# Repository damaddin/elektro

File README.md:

# elektro
Some electronic circuits I made.

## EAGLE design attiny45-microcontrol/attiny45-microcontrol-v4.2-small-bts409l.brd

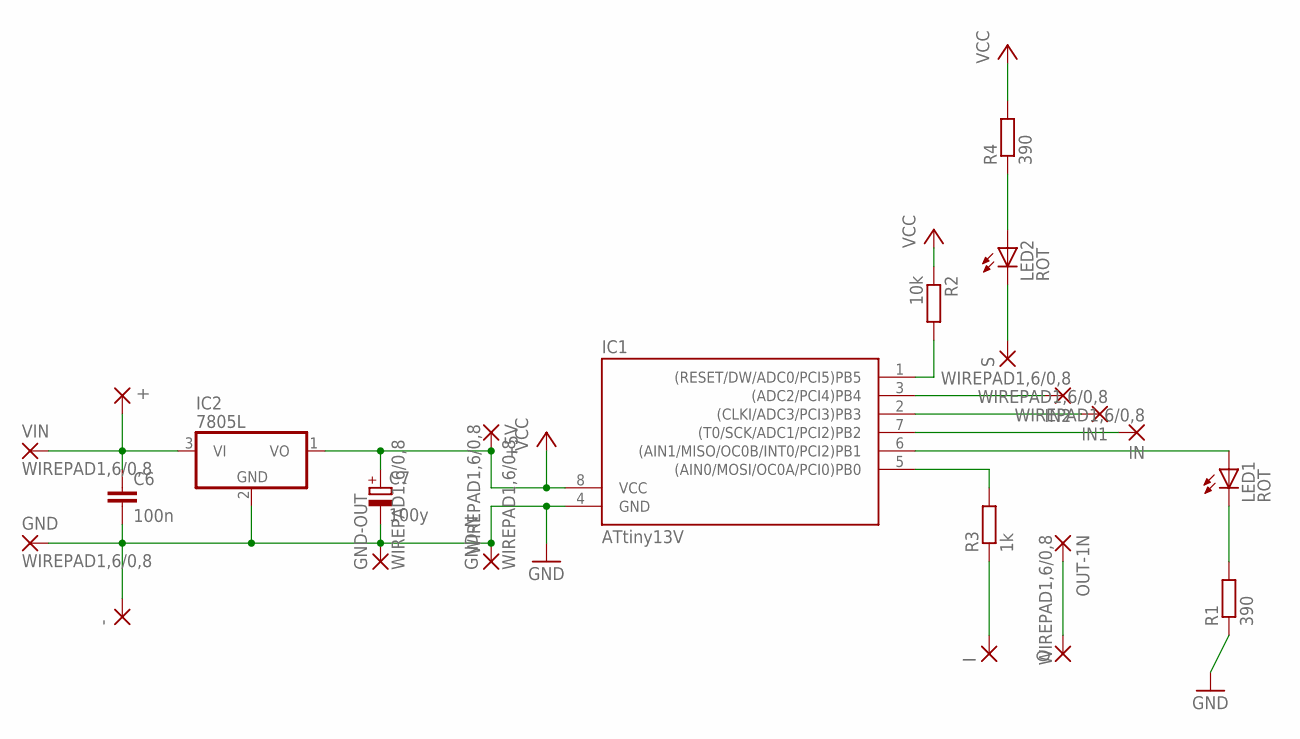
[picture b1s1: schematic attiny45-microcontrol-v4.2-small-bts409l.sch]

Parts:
+: SMD2; SMD1,27-2,54
+5V: WIREPAD1,6/0,8; 1,6/0,8
-: SMD2; SMD1,27-2,54
C6: 100n; C050-035X075
C7: 100y; E2,5-5
GND: WIREPAD1,6/0,8; 1,6/0,8
GND-N: WIREPAD1,6/0,8; 1,6/0,8
GND-OUT: WIREPAD1,6/0,8; 1,6/0,8
I: SMD2; SMD1,27-2,54
IC1: ATtiny13V; DIL08
IC2: 7805L; TO92
IN, IN1, IN2: WIREPAD1,6/0,8; 1,6/0,8
LED1, LED2: ROT; LED3MM
O: SMD2; SMD1,27-2,54
OUT-1N: WIREPAD1,6/0,8; 1,6/0,8
R1, R4: 390; 0204/5
R2: 10k; R1206
R3: 1k; 0207/7
S: SMD2; SMD1,27-2,54
VIN: WIREPAD1,6/0,8; 1,6/0,8

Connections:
GND: -.1, C6.2, C7.-, GND.1, GND-N.1, GND-OUT.1, IC1.4 (GND), IC2.2 (GND), R1.1
unnamed: O.1, OUT-1N.1
unnamed: IC1.2 ((CLKI/ADC3/PCI3)PB3), IN1.1
unnamed: IC1.1 ((RESET/DW/ADC0/PCI5)PB5), R2.2
unnamed: IC1.7 ((T0/SCK/ADC1/PCI2)PB2), IN.1
unnamed: IC1.6 ((AIN1/MISO/OC0B/INT0/PCI2)PB1), LED1.A
unnamed: LED1.K (C), R1.2
unnamed: IC1.3 ((ADC2/PCI4)PB4), IN2.1
unnamed: LED2.A, R4.1
unnamed: IC1.5 ((AIN0/MOSI/OC0A/PCI0)PB0), R3.2
unnamed: I.1, R3.1
unnamed: LED2.K (C), S.1
unnamed: +.1, C6.1, IC2.3 (VI), VIN.1
VCC: +5V.1, C7.+, IC1.8 (VCC), IC2.1 (VO), R2.1, R4.2

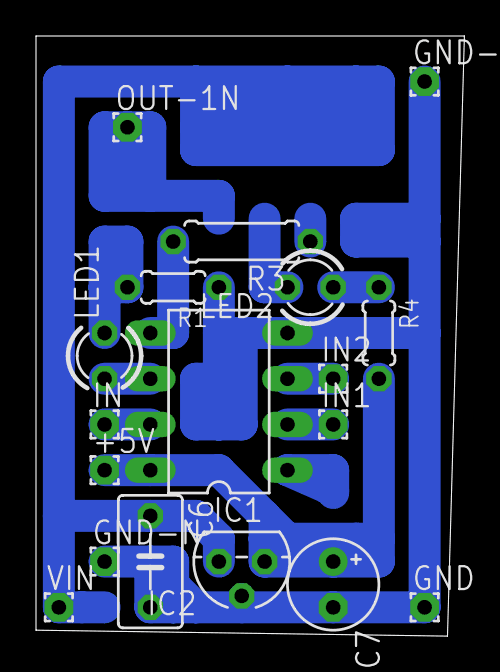
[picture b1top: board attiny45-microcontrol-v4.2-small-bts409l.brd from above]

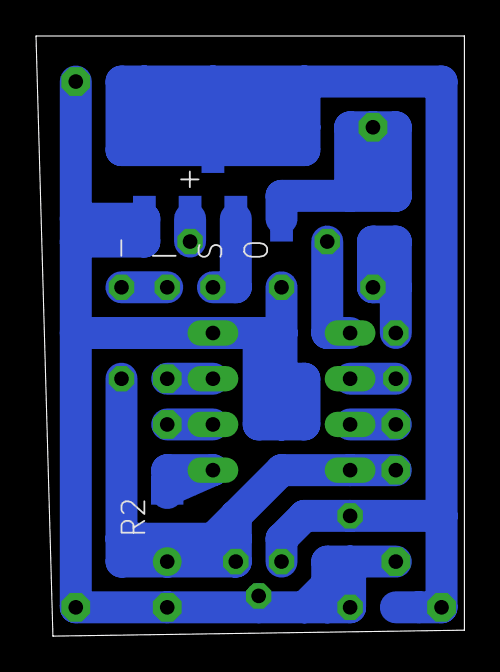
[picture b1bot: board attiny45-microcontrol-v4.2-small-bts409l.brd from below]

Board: 2 copper layers, 23.8 x 33.3 mm, 24 parts (6 on the bottom side), 14 nets.

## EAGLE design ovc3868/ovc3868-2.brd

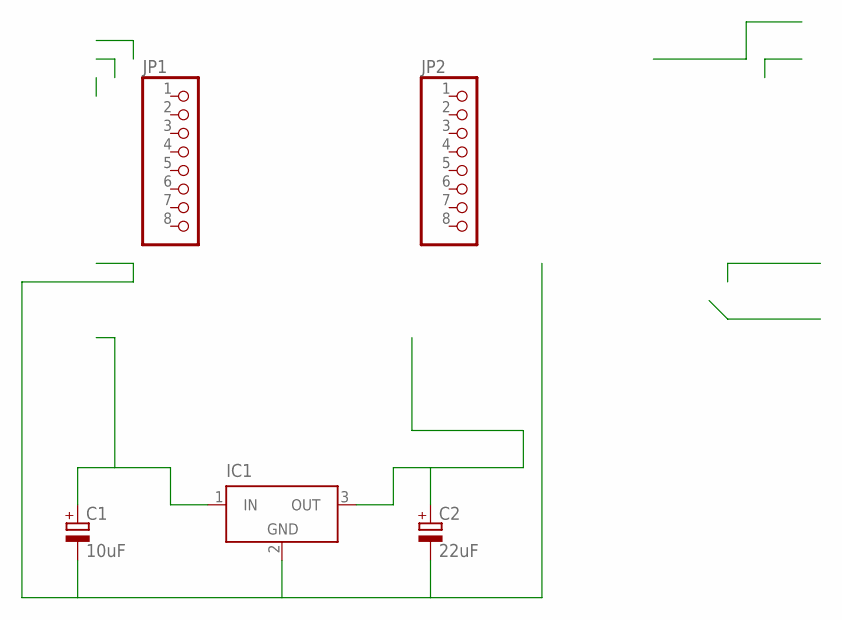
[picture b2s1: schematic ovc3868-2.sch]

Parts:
C1: 10uF; 140CLH-0810
C2: 22uF; 140CLH-0810
IC1: LT1129CST5; SOT223
JP1, JP2: PINHD-1X8; 1X08

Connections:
GND: IC1.4 (GND)
unnamed: C1.+, IC1.1 (IN)
unnamed: C1.-, C2.-, IC1.2 (GND)
unnamed: C2.+, IC1.3 (OUT)

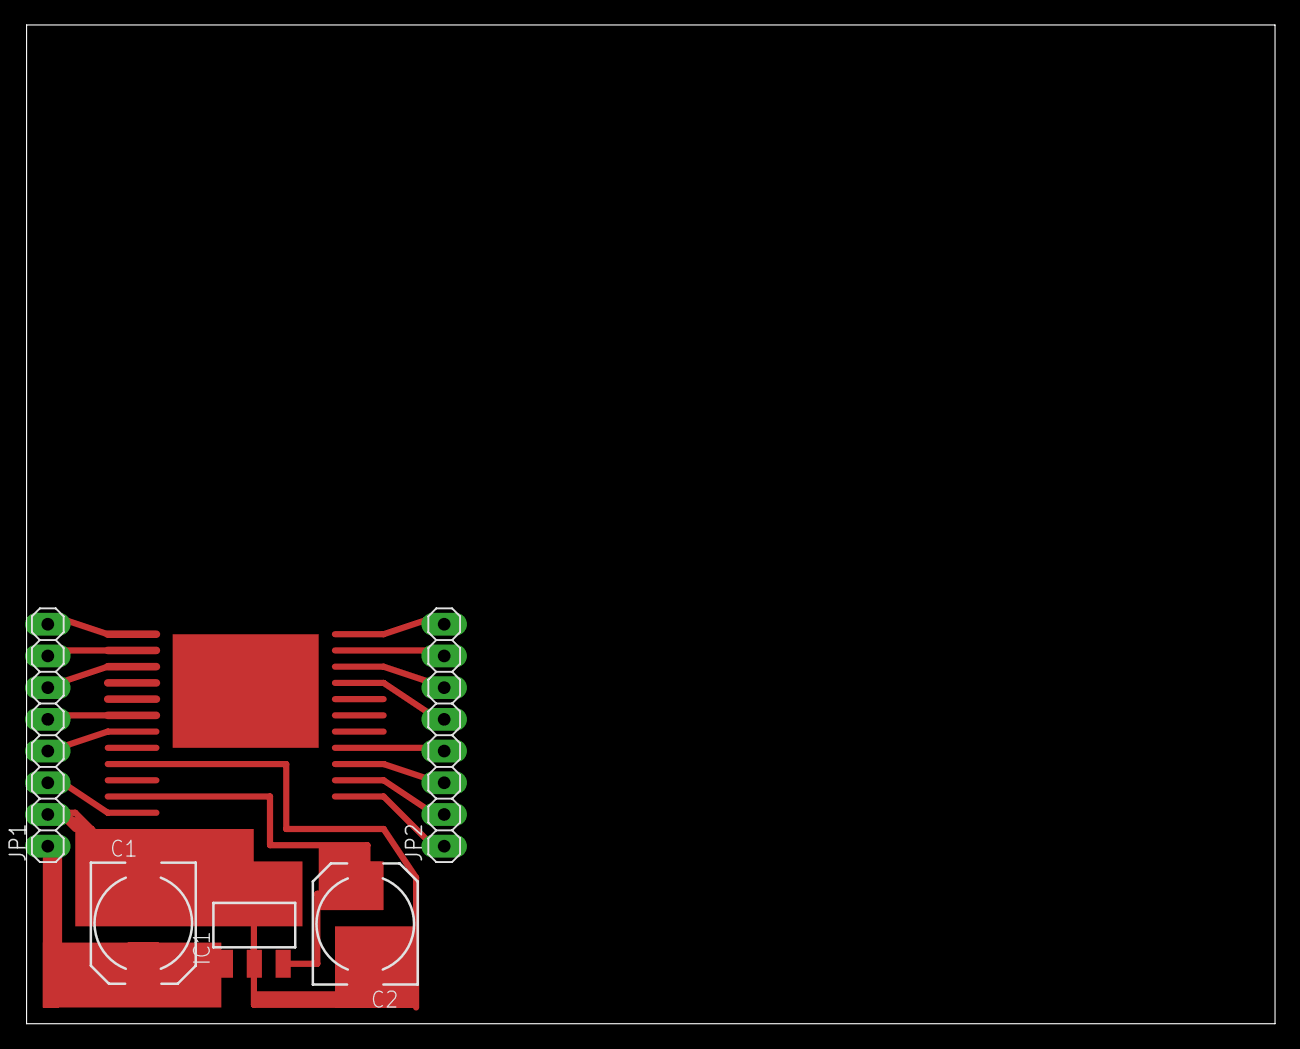
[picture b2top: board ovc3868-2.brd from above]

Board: 2 copper layers, 100.0 x 80.0 mm, 5 parts (0 on the bottom side), 3 nets.

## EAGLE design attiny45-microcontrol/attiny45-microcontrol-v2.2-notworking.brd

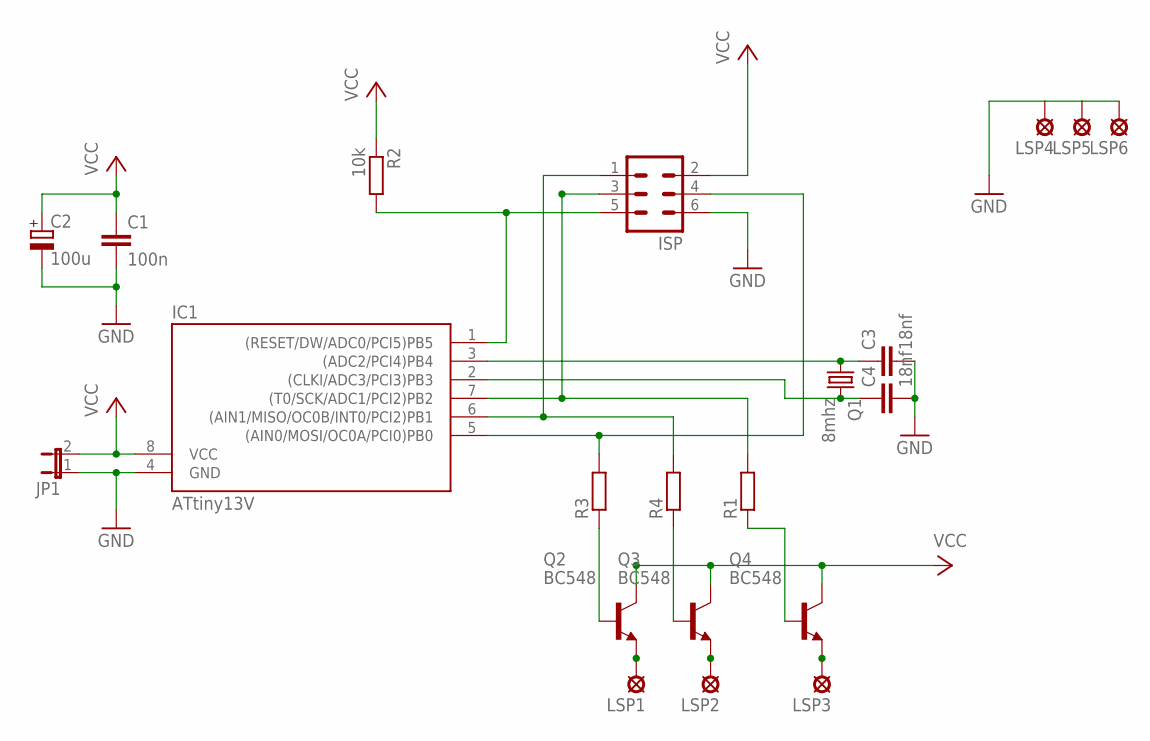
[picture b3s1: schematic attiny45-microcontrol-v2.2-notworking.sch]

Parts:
C1: 100n; C025-025X050
C2: 100u; E2,5-6E
C3, C4: 18nf; C5B2.5
IC1: ATtiny13V; DIL08
ISP: MA03-2
JP1: JP1E; JP1
LSP1, LSP2, LSP3, LSP4, LSP5, LSP6: LSP10
Q1: 8mhz; HC18U-V
Q2, Q3, Q4: BC548; TO92-EBC
R1, R3, R4: R-EU_0204/5; 0204/5
R2: 10k; 0309/12

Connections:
GND: C1.2, C2.-, C3.2, C4.2, IC1.4 (GND), ISP.6, JP1.1, LSP4.MP, LSP5.MP, LSP6.MP
unnamed: Q2.B, R3.1
unnamed: C4.1, IC1.2 ((CLKI/ADC3/PCI3)PB3), Q1.2
unnamed: IC1.1 ((RESET/DW/ADC0/PCI5)PB5), ISP.5, R2.2
unnamed: Q3.B, R4.1
unnamed: IC1.7 ((T0/SCK/ADC1/PCI2)PB2), ISP.3, R1.2
unnamed: IC1.6 ((AIN1/MISO/OC0B/INT0/PCI2)PB1), ISP.1, R4.2
unnamed: Q4.B, R1.1
unnamed: C3.1, IC1.3 ((ADC2/PCI4)PB4), Q1.1
unnamed: IC1.5 ((AIN0/MOSI/OC0A/PCI0)PB0), ISP.4, R3.2
unnamed: LSP1.MP, Q2.E
unnamed: LSP2.MP, Q3.E
unnamed: LSP3.MP, Q4.E
VCC: C1.1, C2.+, IC1.8 (VCC), ISP.2, JP1.2, Q2.C, Q3.C, Q4.C, R2.1

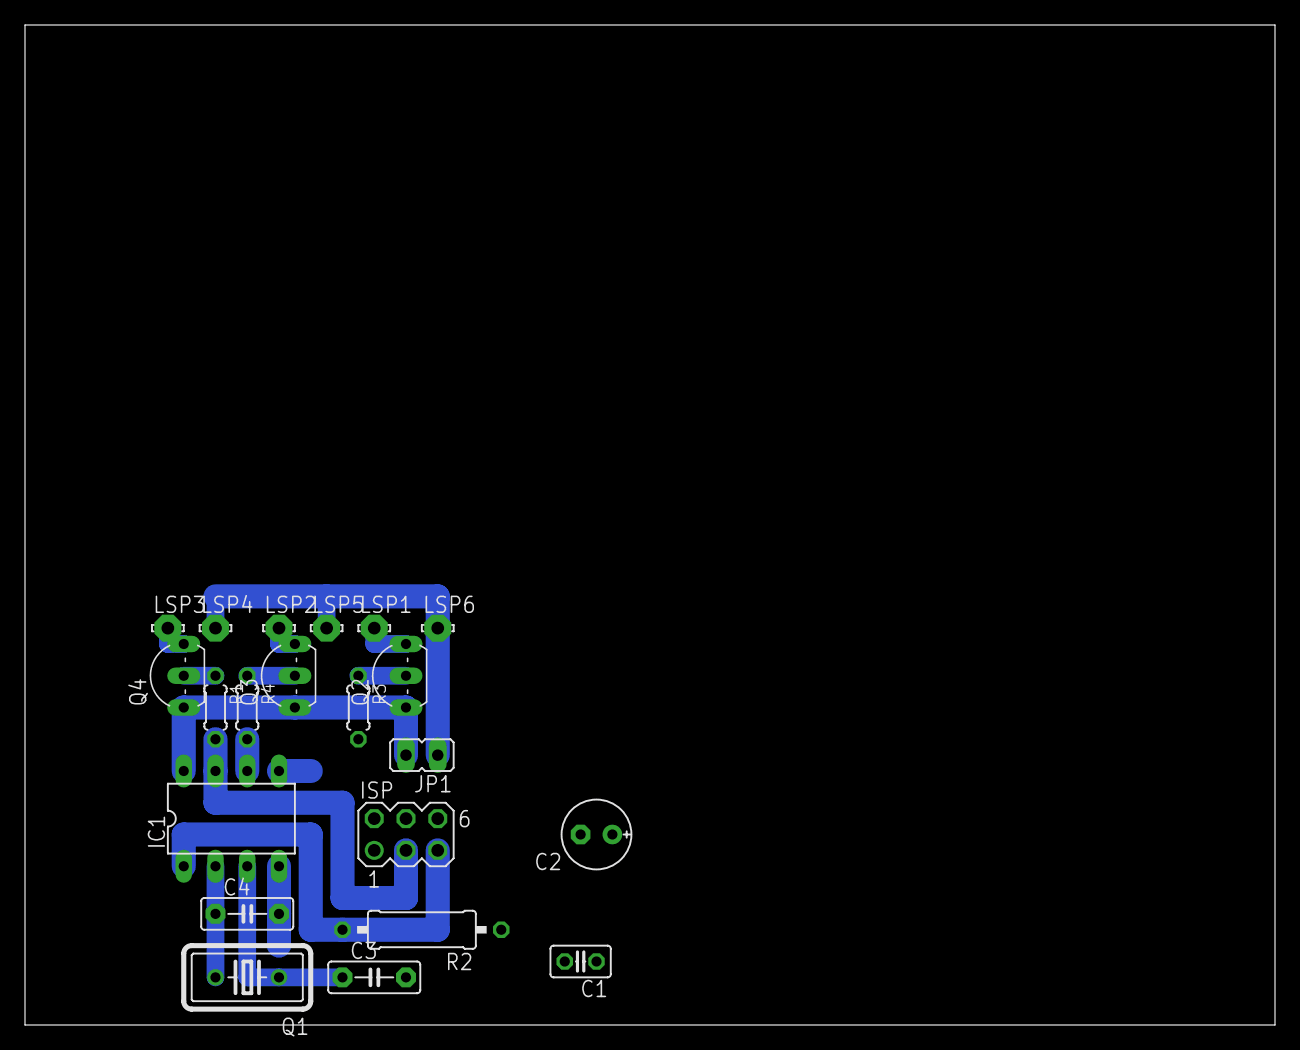
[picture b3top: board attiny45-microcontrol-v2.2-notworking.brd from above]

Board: 2 copper layers, 100.0 x 80.0 mm, 21 parts (0 on the bottom side), 14 nets.

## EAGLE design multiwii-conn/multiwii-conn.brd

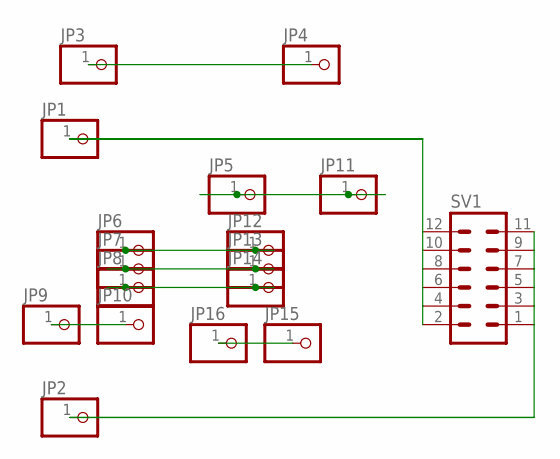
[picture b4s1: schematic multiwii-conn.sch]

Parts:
JP1, JP2, JP3, JP4, JP5, JP6, JP7, JP8, JP9, JP10, JP11, JP12, JP13, JP14, JP15, JP16: PINHD-1X1; 1X01
SV1: MA06-2

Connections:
unnamed: JP5.1, JP11.1
unnamed: JP6.1, JP12.1
unnamed: JP7.1, JP13.1
unnamed: JP8.1, JP14.1
unnamed: JP15.1, JP16.1
unnamed: JP9.1, JP10.1
unnamed: JP3.1, JP4.1
unnamed: JP1.1, SV1.2, SV1.4, SV1.6, SV1.8, SV1.10, SV1.12
unnamed: JP2.1, SV1.1, SV1.3, SV1.5, SV1.7, SV1.9, SV1.11

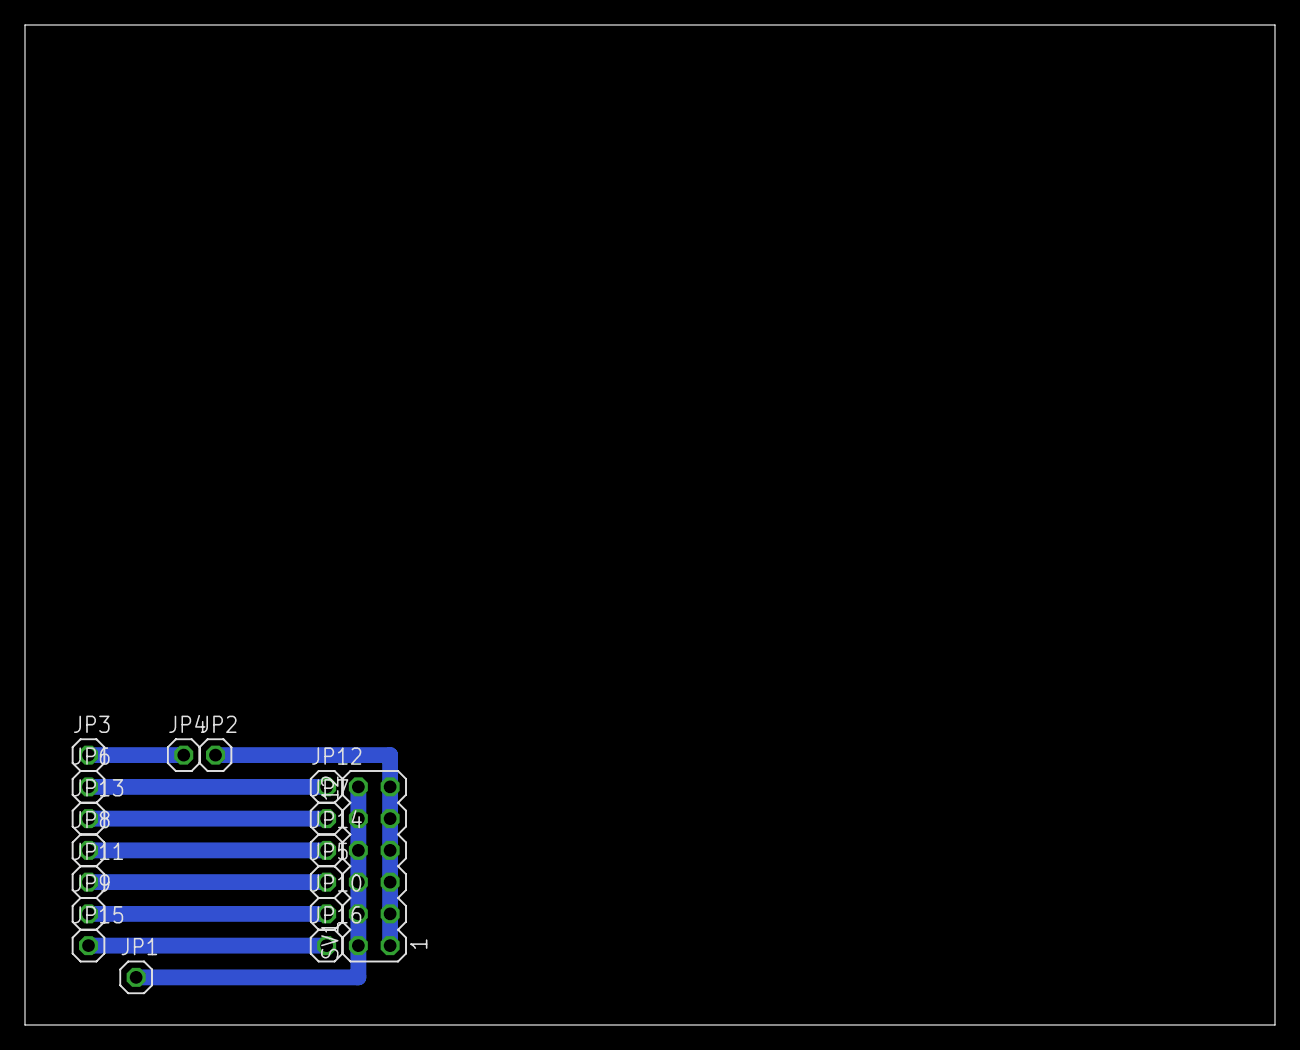
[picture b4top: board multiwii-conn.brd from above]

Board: 2 copper layers, 100.0 x 80.0 mm, 17 parts (0 on the bottom side), 9 nets.

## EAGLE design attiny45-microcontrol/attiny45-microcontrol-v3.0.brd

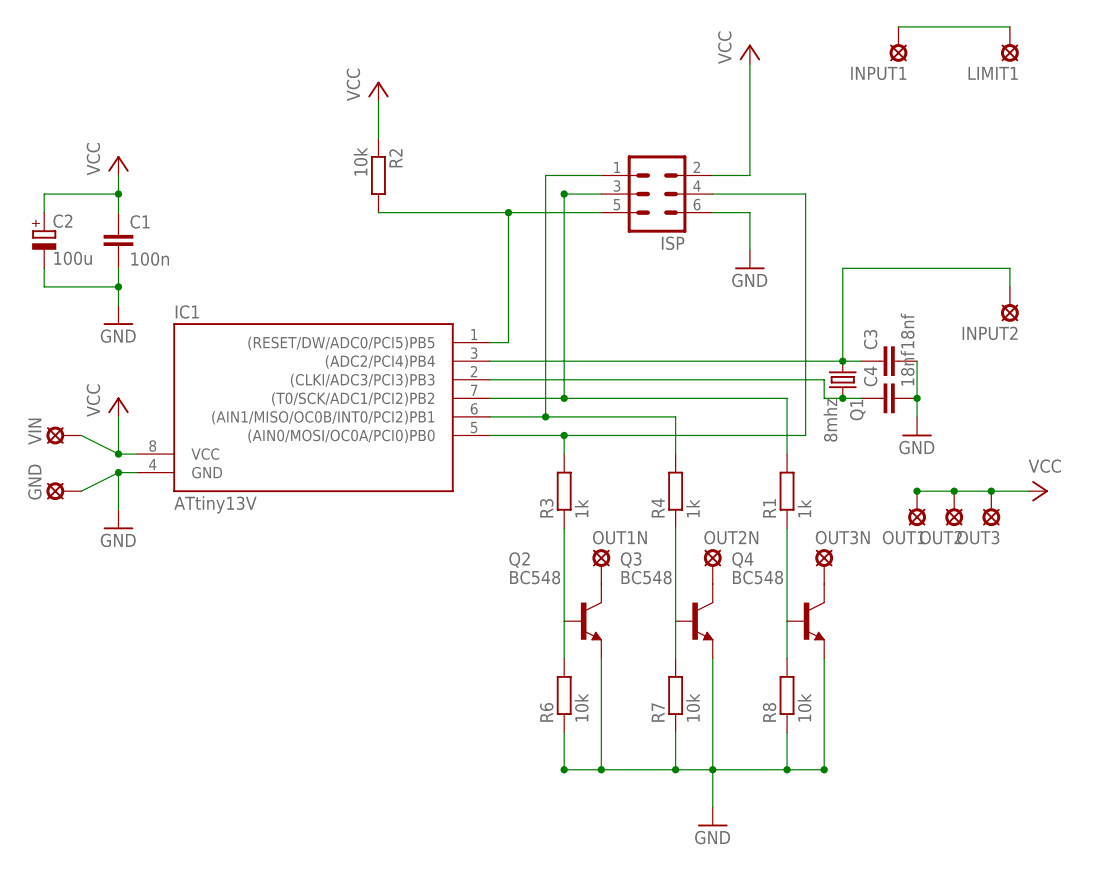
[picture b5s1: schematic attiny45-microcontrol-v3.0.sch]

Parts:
C1: 100n; C025-025X050
C2: 100u; E2,5-6E
C3, C4: 18nf; C5B2.5
GND: LSP10
IC1: ATtiny13V; DIL08
INPUT1, INPUT2: LSP10
ISP: MA03-2
LIMIT1: LSP10
OUT1, OUT1N, OUT2, OUT2N, OUT3, OUT3N: LSP10
Q1: 8mhz; HC18U-V
Q2, Q3, Q4: BC548; TO92-EBC
R1, R3, R4: 1k; 0204/7
R2, R6, R7, R8: 10k; 0204V
VIN: LSP10

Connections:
GND: C1.2, C2.-, C3.2, C4.2, GND.MP, IC1.4 (GND), ISP.6, Q2.E, Q3.E, Q4.E, R6.1, R7.1, R8.1
unnamed: Q2.B, R3.1, R6.2
unnamed: C4.1, IC1.2 ((CLKI/ADC3/PCI3)PB3), Q1.2
unnamed: IC1.1 ((RESET/DW/ADC0/PCI5)PB5), ISP.5, R2.2
unnamed: Q3.B, R4.1, R7.2
unnamed: IC1.7 ((T0/SCK/ADC1/PCI2)PB2), ISP.3, R1.2
unnamed: IC1.6 ((AIN1/MISO/OC0B/INT0/PCI2)PB1), ISP.1, R4.2
unnamed: Q4.B, R1.1, R8.2
unnamed: C3.1, IC1.3 ((ADC2/PCI4)PB4), INPUT2.MP, Q1.1
unnamed: INPUT1.MP, LIMIT1.MP
unnamed: IC1.5 ((AIN0/MOSI/OC0A/PCI0)PB0), ISP.4, R3.2
unnamed: OUT3N.MP, Q4.C
unnamed: OUT2N.MP, Q3.C
unnamed: OUT1N.MP, Q2.C
VCC: C1.1, C2.+, IC1.8 (VCC), ISP.2, OUT1.MP, OUT2.MP, OUT3.MP, R2.1, VIN.MP

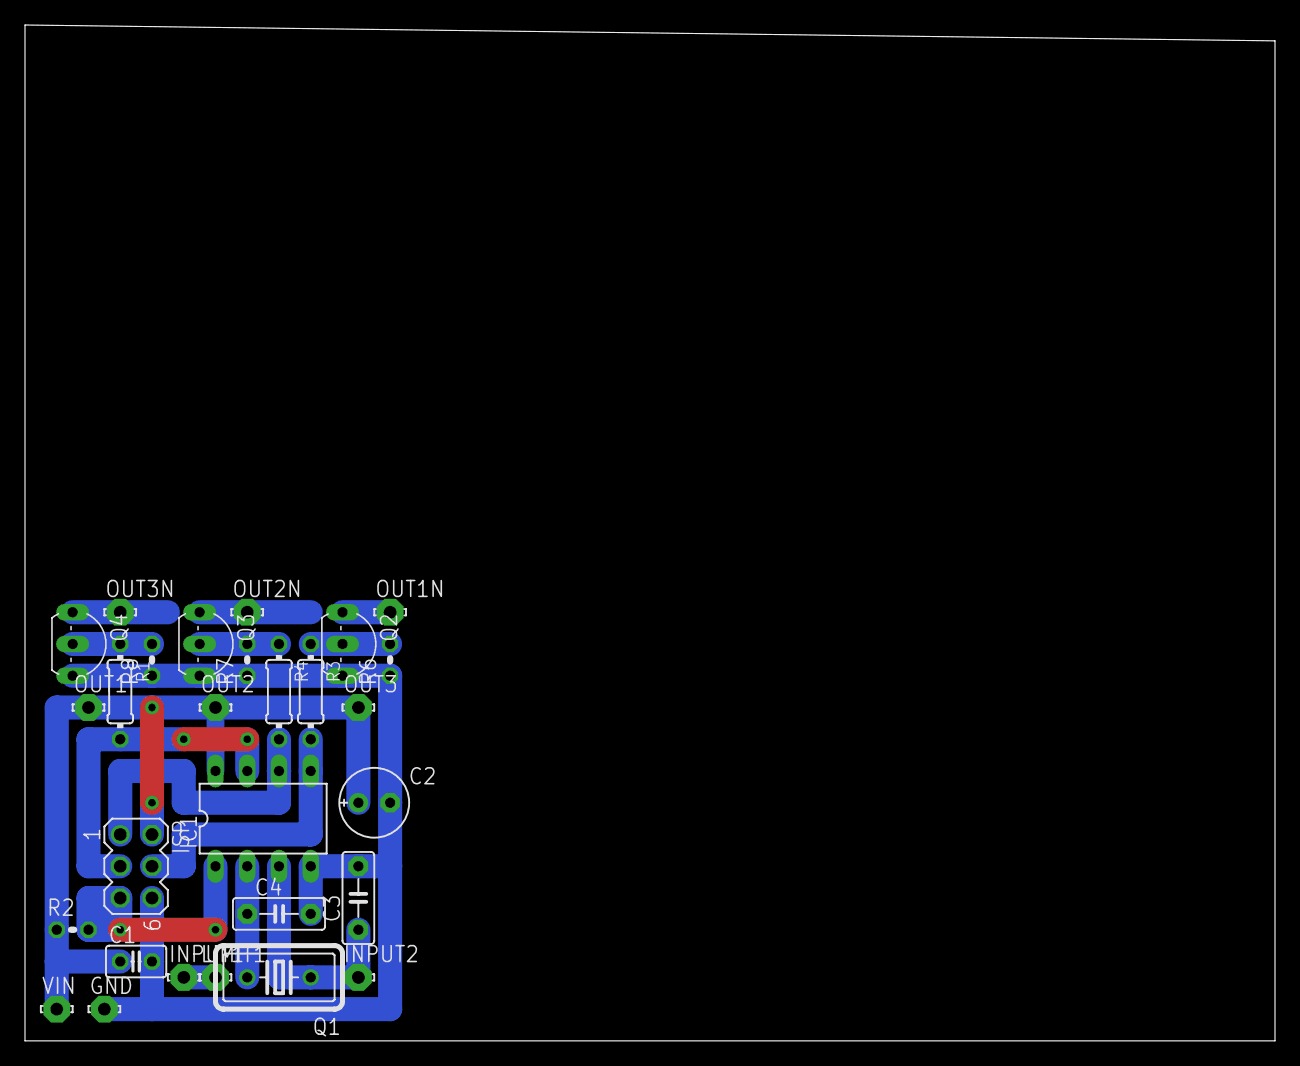
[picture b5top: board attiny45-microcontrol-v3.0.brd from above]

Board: 2 copper layers, 100.0 x 81.3 mm, 28 parts (0 on the bottom side), 15 nets.

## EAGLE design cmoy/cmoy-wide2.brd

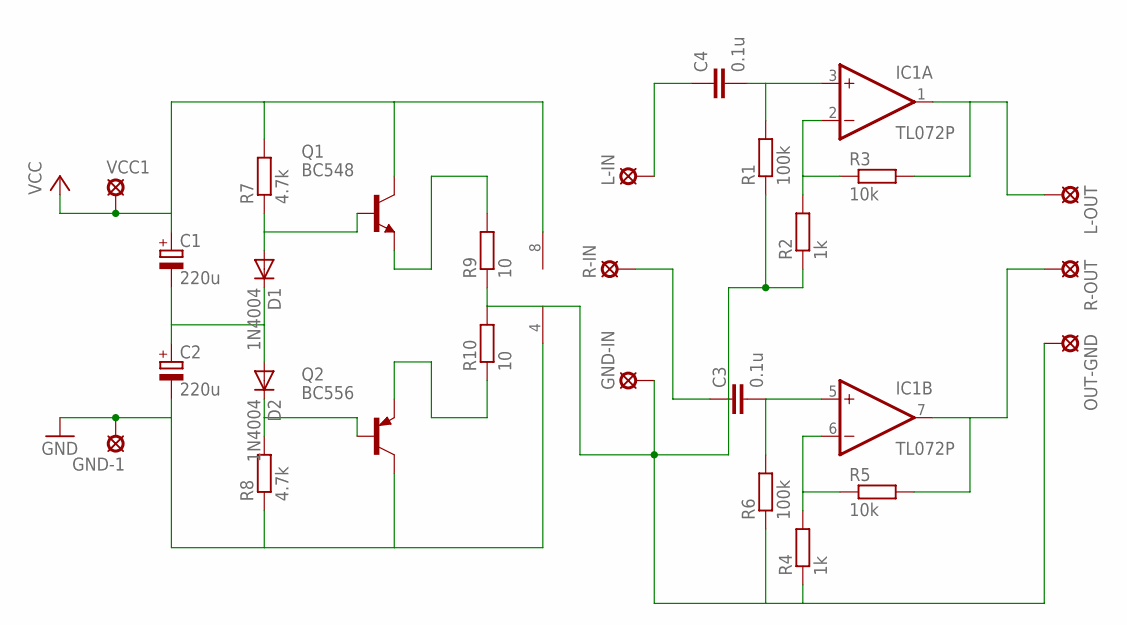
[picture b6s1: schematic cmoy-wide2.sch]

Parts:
C1, C2: 220u; E2,5-6
C3, C4: 0.1u; C075-042X103
D1, D2: 1N4004; DO41-10
GND-1: LSP10
GND-IN: LSP10
IC1: TL072P; DIL08
L-IN: LSP10
L-OUT: LSP10
OUT-GND: LSP10
Q1: BC548; TO92-EBC
Q2: BC556; TO92-EBC
R1, R6: 100k; 0207/10
R2, R4: 1k; 0207/10
R3, R5: 10k; 0207/10
R7, R8: 4.7k; 0207/10
R9, R10: 10; 0207/10
R-IN: LSP10
R-OUT: LSP10
VCC1: LSP10

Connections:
GND: C2.-, GND-1.MP, IC1.4 (V-), Q2.C, R8.1
unnamed: C1.-, C2.+, D1.C, D2.A
unnamed: D2.C, Q2.B, R8.2
unnamed: D1.A, Q1.B, R7.1
unnamed: GND-IN.MP, OUT-GND.MP, R1.1, R2.1, R4.1, R6.1, R9.1, R10.2
unnamed: Q1.E, R9.2
unnamed: Q2.E, R10.1
unnamed: IC1.2 (-IN), R2.2, R3.1
unnamed: IC1.1 (OUT), L-OUT.MP, R3.2
unnamed: C4.2, IC1.3 (+IN), R1.2
unnamed: C4.1, L-IN.MP
unnamed: IC1.7 (OUT), R5.2, R-OUT.MP
unnamed: IC1.6 (-IN), R4.2, R5.1
unnamed: C3.2, IC1.5 (+IN), R6.2
unnamed: C3.1, R-IN.MP
VCC: C1.+, IC1.8 (V+), Q1.C, R7.2, VCC1.MP

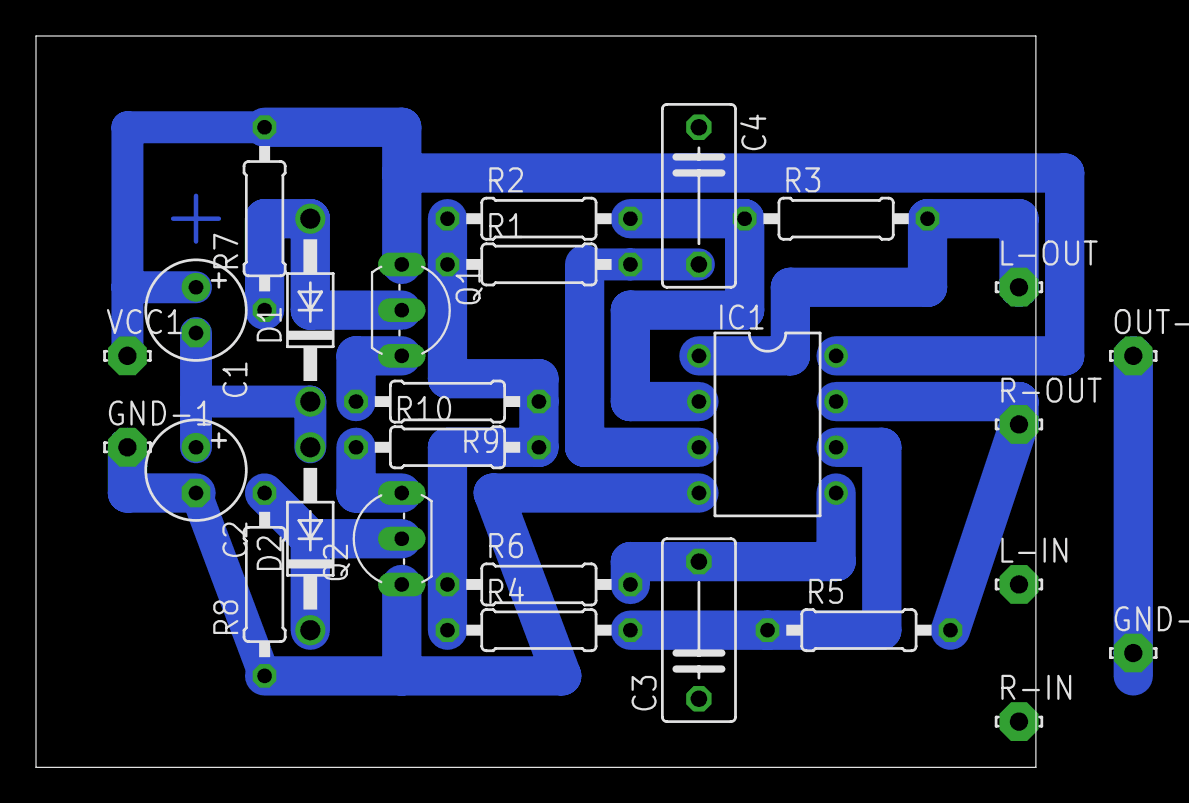
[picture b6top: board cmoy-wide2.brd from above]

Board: 2 copper layers, 55.5 x 40.6 mm, 27 parts (0 on the bottom side), 16 nets.

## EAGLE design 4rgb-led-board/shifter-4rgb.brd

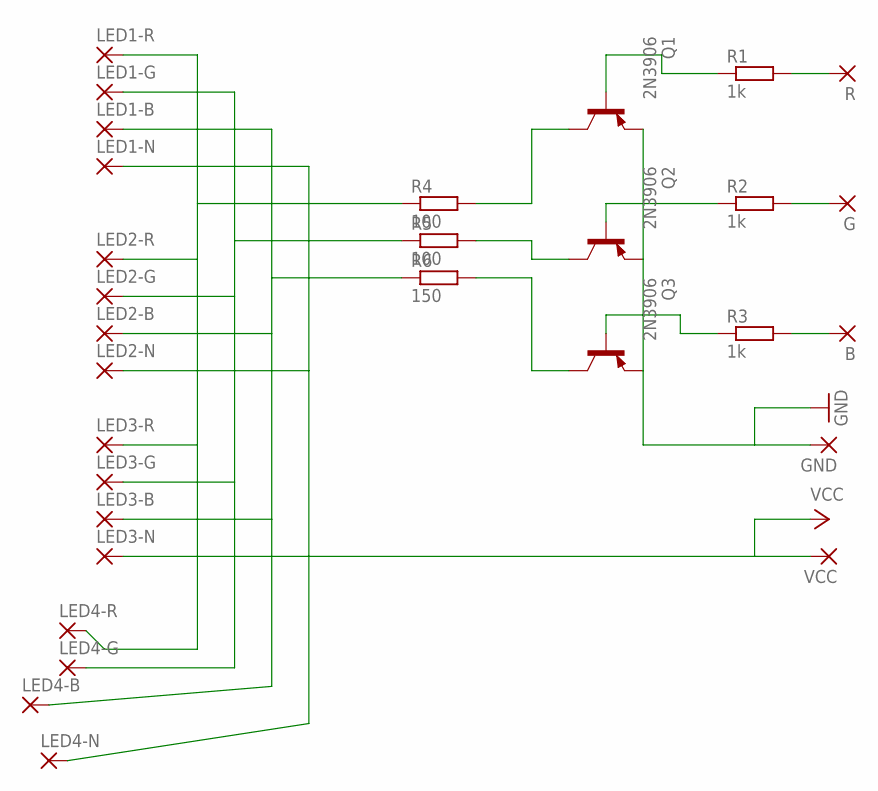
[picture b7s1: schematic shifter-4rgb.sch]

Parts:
B: 2,54/0,8
G: 2,54/0,8
GND: 2,54/0,8
LED1-B, LED1-G, LED1-N, LED1-R, LED2-B, LED2-G, LED2-N, LED2-R, LED3-B, LED3-G, LED3-N, LED3-R, LED4-B, LED4-G, LED4-N, LED4-R: 2,54/0,8
Q1, Q2, Q3: 2N3906; TO92
R: 2,54/0,8
R1, R2, R3: 1k; 0207/2V
R4: 100; 0207/2V
R5: 100; 0207/7
R6: 150; 0207/2V
VCC: 2,54/0,8

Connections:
GND: GND.1, Q1.3 (E), Q2.3 (E), Q3.3 (E)
unnamed: LED1-R.1, LED2-R.1, LED3-R.1, LED4-R.1, R4.1
unnamed: LED1-G.1, LED2-G.1, LED3-G.1, LED4-G.1, R5.1
unnamed: LED1-B.1, LED2-B.1, LED3-B.1, LED4-B.1, R6.1
unnamed: Q1.1 (C), R4.2
unnamed: Q2.1 (C), R5.2
unnamed: Q3.1 (C), R6.2
unnamed: Q1.2 (B), R1.1
unnamed: R.1, R1.2
unnamed: G.1, R2.2
unnamed: B.1, R3.2
unnamed: Q2.2 (B), R2.1
unnamed: Q3.2 (B), R3.1
VCC: LED1-N.1, LED2-N.1, LED3-N.1, LED4-N.1, VCC.1

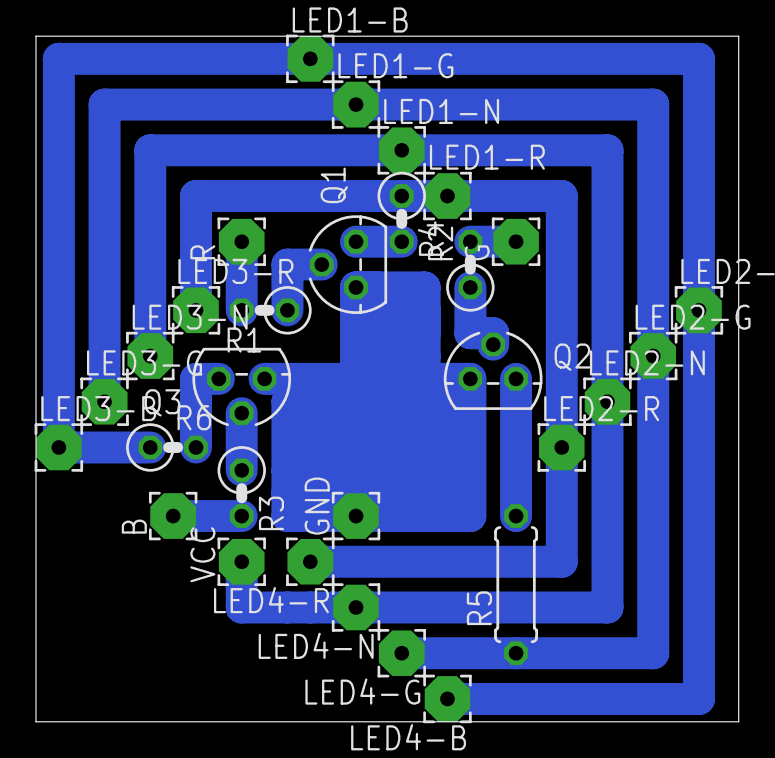
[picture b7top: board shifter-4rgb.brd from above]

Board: 2 copper layers, 39.0 x 38.1 mm, 30 parts (0 on the bottom side), 14 nets.

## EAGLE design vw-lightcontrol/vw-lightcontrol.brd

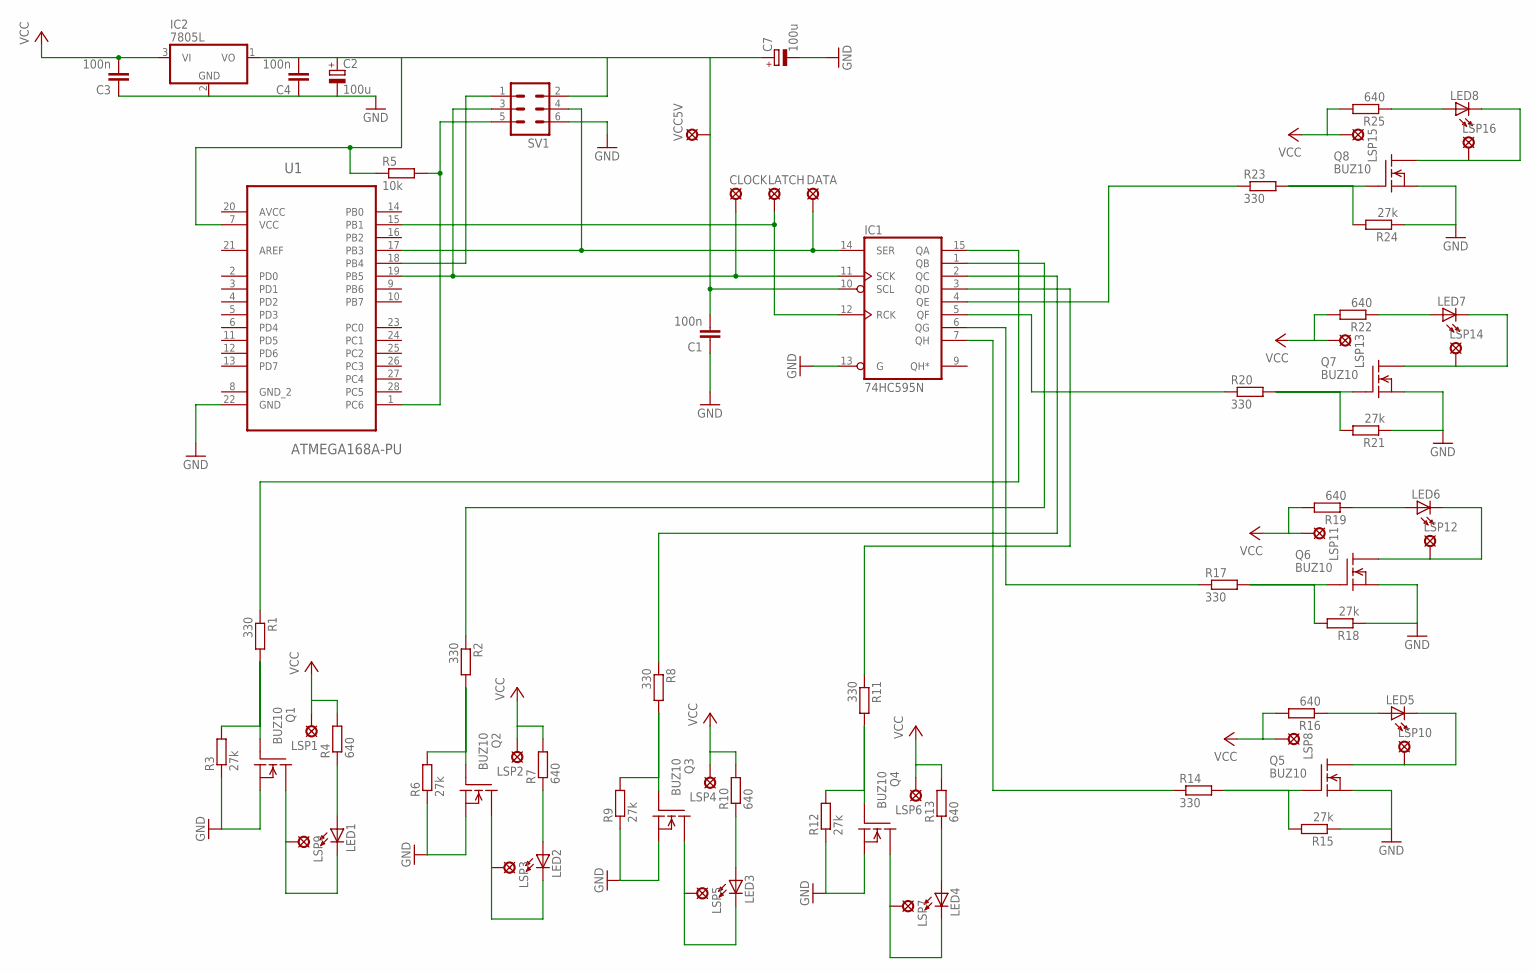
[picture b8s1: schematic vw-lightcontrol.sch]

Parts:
C1, C3, C4: 100n; C2.5-4
C2, C7: 100u; E2,5-6E
CLOCK: LSP10
DATA: LSP10
IC1: 74HC595N; DIL16
IC2: 7805L; TO92
LATCH: LSP10
LED1, LED2, LED3, LED4, LED5, LED6, LED7, LED8: LED3MM
LSP1, LSP2, LSP3, LSP4, LSP5, LSP6, LSP7, LSP8, LSP9, LSP10, LSP11, LSP12, LSP13, LSP14, LSP15, LSP16: LSP10
Q1, Q2, Q3, Q4, Q5, Q6, Q7, Q8: BUZ10; TO220
R1, R2, R8, R11, R14, R17, R20, R23: 330; 0207/10
R3, R6, R9, R12, R15, R18, R21, R24: 27k; 0207/10
R4, R7, R10, R13, R16, R19, R22, R25: 640; 0207/10
R5: 10k; 0207/10
SV1: MA03-2
U1: ATMEGA168A-PU; DIP254P762X457-28
VCC5V: LSP10

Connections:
AVCC: U1.20 (AVCC)
GND: C2.-, C3.1, C4.1, IC1.13 (G), IC2.2 (GND), Q1.3 (S), Q2.3 (S), Q3.3 (S), Q4.3 (S), Q5.3 (S), Q6.3 (S), Q7.3 (S), Q8.3 (S), R3.1, R6.1, R9.1, R12.1, R15.1, R18.1, R21.1, R24.1, SV1.6, U1.22 (GND)
unnamed: LED1.A, R4.1
unnamed: Q1.1 (G), R1.2, R3.2
unnamed: LED1.K (C), LSP9.MP, Q1.2 (D)
unnamed: IC1.15 (QA), R1.1
unnamed: LED2.A, R7.1
unnamed: C3.2, IC1.16 (VCC), IC2.3 (VI), LSP1.MP, LSP2.MP, LSP4.MP, LSP6.MP, LSP8.MP, LSP11.MP, LSP13.MP, LSP15.MP, R4.2, R7.2, R10.2, R13.2, R16.2, R19.2, R22.2, R25.2
unnamed: C1.2, C2.+, C4.2, C7.+, IC1.10 (SCL), IC2.1 (VO), R5.1, SV1.2, U1.7 (VCC), VCC5V.MP
unnamed: Q2.1 (G), R2.2, R6.2
unnamed: LED2.K (C), LSP3.MP, Q2.2 (D)
unnamed: IC1.1 (QB), R2.1
unnamed: LED3.A, R10.1
unnamed: Q3.1 (G), R8.2, R9.2
unnamed: LED3.K (C), LSP5.MP, Q3.2 (D)
unnamed: IC1.2 (QC), R8.1
unnamed: LED4.A, R13.1
unnamed: Q4.1 (G), R11.2, R12.2
unnamed: LED4.K (C), LSP7.MP, Q4.2 (D)
unnamed: IC1.3 (QD), R11.1
unnamed: LED5.A, R16.1
unnamed: R5.2, SV1.5, U1.1 (PC6)
unnamed: Q5.1 (G), R14.2, R15.2
unnamed: DATA.MP, IC1.14 (SER), SV1.4, U1.17 (PB3)
unnamed: SV1.1, U1.18 (PB4)
unnamed: LED5.K (C), LSP10.MP, Q5.2 (D)
unnamed: IC1.7 (QH), R14.1
unnamed: LED6.A, R19.1
unnamed: Q6.1 (G), R17.2, R18.2
unnamed: LED6.K (C), LSP12.MP, Q6.2 (D)
unnamed: IC1.6 (QG), R17.1
unnamed: LED7.A, R22.1
unnamed: Q7.1 (G), R20.2, R21.2
unnamed: LED7.K (C), LSP14.MP, Q7.2 (D)
unnamed: IC1.5 (QF), R20.1
unnamed: LED8.A, R25.1
unnamed: Q8.1 (G), R23.2, R24.2
unnamed: LED8.K (C), LSP16.MP, Q8.2 (D)
unnamed: IC1.4 (QE), R23.1
unnamed: CLOCK.MP, IC1.11 (SCK), SV1.3, U1.19 (PB5)
unnamed: C1.1, C7.-, IC1.8 (GND)
unnamed: IC1.12 (RCK), LATCH.MP, U1.15 (PB1)

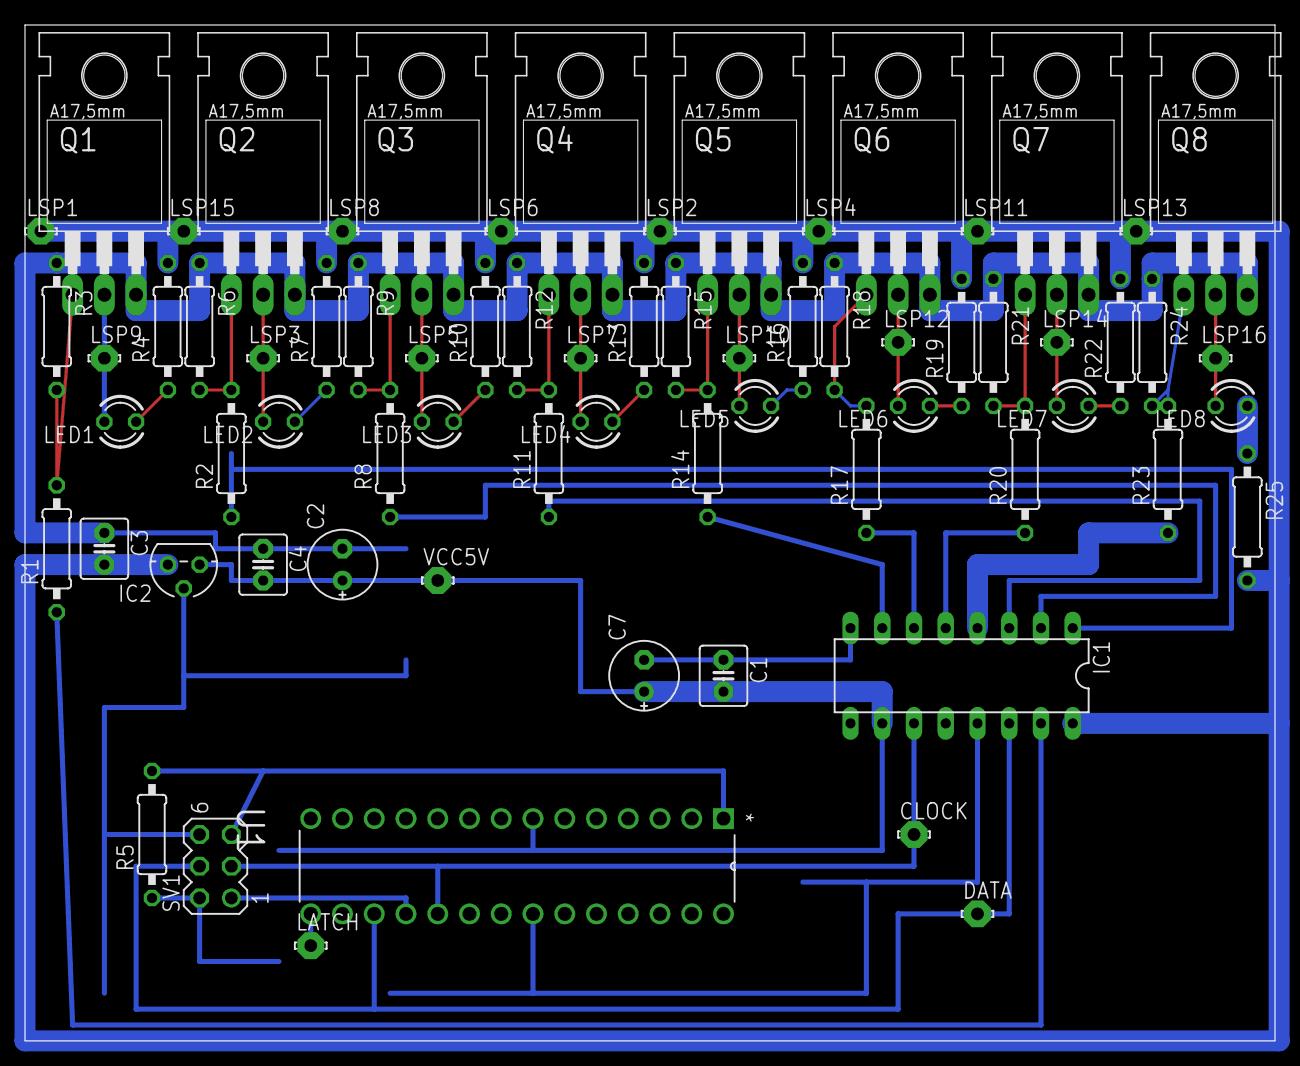
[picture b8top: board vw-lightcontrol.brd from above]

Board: 2 copper layers, 100.0 x 81.3 mm, 70 parts (0 on the bottom side), 41 nets.

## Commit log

2016-05-29 initial import
2016-06-03 bts409l version
